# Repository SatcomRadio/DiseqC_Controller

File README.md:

# DiseqC_Controller
Controller board based on a ESP32 to control DiseqC rotors

### This repo is a work in progress! Eveything is subject to change!

#### Please make sure to visit the [satcom radio website](https://satcomradio.github.io/)

----

### ESP32 image

First install nanoframework:  
In a powershell window write: `dotnet tool install -g nanoff`  
Check [this link](https://github.com/nanoframework/nanoFirmwareFlasher) for more information

If you want to build the code:  

Install nanoframework on the ESP32 C3 with the command:
`nanoff --update --target XIAO_ESP32C3 --serialport COM{YOUR NUMBER} --masserase`  

Then compile the code and upload  

If you only want to flash the Diseq controller to your ESP32:  

`nanoff --target XIAO_ESP32C3 --update --serialport COM{YOUR NUMBER} --deploy --image "c:\PATH_TO_YOUR\DiseqC.bin"`  

----

### General info

Before connecting the rotor, ADJUST THE VOLTAGE to around 18v max!  
To do so, send the command to move the rotor, monitor the voltage in the SMA output and adjust the trimmer.

When turning the controller on the status led will flash fast to indicate that it's trying to connect to your wifi.

When there's no wifi configured or it didn't managed to connect, the ESP32 will create it's own access point and the led will flash slowly.  
Connect to it and use the rotor controller at:
`http://192.168.5.1`

If the controller manages to connect to your wifi, the status led will be on continuously.  
Check it's IP address on your modem page.

You can also send an angle using a POST to the following API:

The potentiometer works in intervals of 20º. It's not linear due to limitations of the ESP32
You can check the current value on the website and mark it down with a pen in the metal case.

----

### Construction:

Make sure to trim the solder fillets at the bottom of the step up converter. 
It's the only difficult part to sodler as you need that it makes a good contact with the tabs at the bottom

Fold the leds before soldering them as shown in previous pictures.

----

### Ordering the PCB:

Download the Gerber file from this repo and order it a jlcpcb with the default options.  
The only option I've changed is to remove the manufacture code mark

----

### BOM:

- [80x32x32 mm case](https://aliexpress.com/item/1005005484479479.html)
- [ESP32 C3 super mini with antenna port](https://aliexpress.com/item/1005007785335513.html)
- [SMA Edge connector](https://aliexpress.com/item/1005007013777316.html)
- [UFL pigtail](https://aliexpress.com/item/1005009270045616.html)
- 2.54mm Header pins (usually included with the ESP32)
- 0805 capacitor 10u
- 0805 capacitor 4.7n
- 0805 capacitor 47n
- 0805 capacitor 10u
- 0805 resistor 4k7
- 0805 resistor 100
- 0805 resistor 50
- 0805 resistor 10k
- 0805 resistor 150
- 0805 resistor 20
- [12x12 1m CDRH125 inductor](https://aliexpress.com/item/1005002743197146.html)
- [3mm 3v led](https://aliexpress.com/item/1005006269054479.html)
- [AO4484](https://aliexpress.com/item/1005009121264682.html)
- [TL081CDR](https://aliexpress.com/item/1005007336116897.html)
- [MT-3608 Step up module](https://aliexpress.com/item/1005007723986240.html)
- [10k potentiometer with button](https://aliexpress.com/item/1005009506482081.html)

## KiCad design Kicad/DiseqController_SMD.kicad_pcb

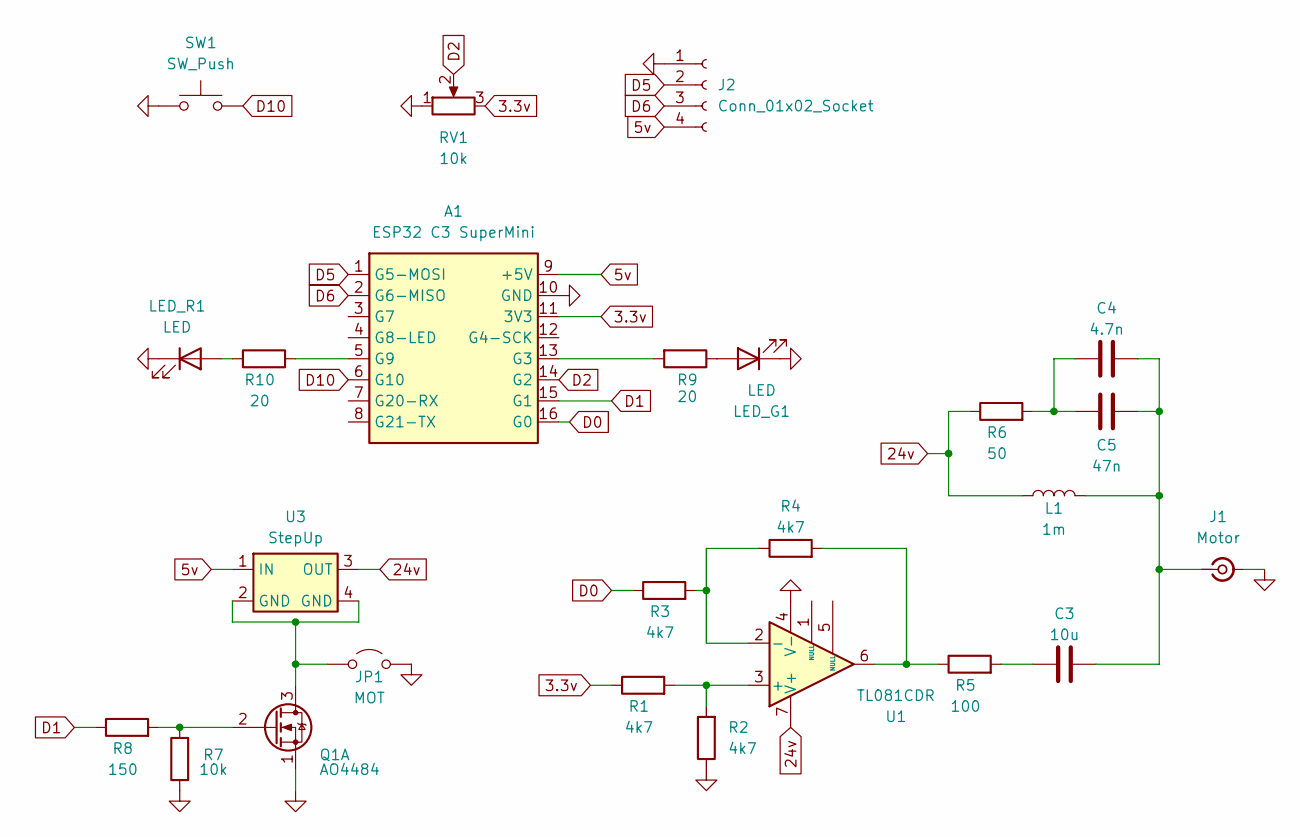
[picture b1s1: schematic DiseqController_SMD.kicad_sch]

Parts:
A1: ESP32 C3 SuperMini; ESP32SuperMini
C3: 10u; C_0805_2012Metric_Pad1.18x1.45mm_HandSolder
C4: 4.7n; C_0805_2012Metric_Pad1.18x1.45mm_HandSolder
C5: 47n; C_0805_2012Metric_Pad1.18x1.45mm_HandSolder
J1: Motor; SMA_Edge
J2: Conn_01x02_Socket; PinHeader_1x04_P2.54mm_Vertical
JP1: MOT; SolderJumper-2_P1.3mm_Open_Pad1.0x1.5mm
L1: 1m; Indcutor_12x12mm_H6mm
LED_G1: LED; Bent_LED_3mm
LED_R1: LED; Bent_LED_3mm
Q1: AO4484
R1, R2, R3, R4: 4k7; R_0805_2012Metric_Pad1.20x1.40mm_HandSolder
R5: 100; R_0805_2012Metric_Pad1.20x1.40mm_HandSolder
R6: 50; R_0805_2012Metric_Pad1.20x1.40mm_HandSolder
R7: 10k; R_0805_2012Metric_Pad1.20x1.40mm_HandSolder
R8: 150; R_0805_2012Metric_Pad1.20x1.40mm_HandSolder
R9, R10: 20; R_0805_2012Metric_Pad1.20x1.40mm_HandSolder
RV1: 10k; PinHeader_1x03_P2.54mm_Vertical
SW1: SW_Push; PinHeader_1x02_P2.54mm_Vertical
U1: TL081CDR; SOIC-8_3.9x4.9mm_P1.27mm
U3: StepUp; StepUp_2A

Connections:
3.3v: A1.11 (3V3), R1.1, RV1.3
5v: A1.9 (+5V), J2.4, U3.1 (IN)
24v: L1.1, R6.1, U1.7 (V+), U3.3 (OUT)
D0: A1.16 (G0), R3.1
D1: A1.15 (G1), R8.1
D2: A1.14 (G2), RV1.2
D5: A1.1 (G5-MOSI), J2.2
D6: A1.2 (G6-MISO), J2.3
D10: A1.6 (G10), SW1.2
GND: A1.10 (GND), J1.2 (Ext), J2.1, JP1.2 (B), LED_G1.1 (K), LED_R1.1 (K), Q1.1 (S1), R2.1, R7.1, RV1.1, SW1.1, U1.4 (V-)
unnamed: A1.13 (G3), R9.2
unnamed: A1.5 (G9), R10.2
unnamed: C3.2, R5.2
unnamed: C4.2, C5.2, R6.2
unnamed: C3.1, C4.1, C5.1, J1.1 (In), L1.2
unnamed: JP1.1 (A), Q1.3 (D1), U3.2 (GND), U3.4 (GND)
unnamed: LED_G1.2 (A), R9.1
unnamed: LED_R1.2 (A), R10.1
unnamed: Q1.2 (G1), R7.2, R8.2
unnamed: R4.2, R5.1, U1.6
unnamed: R1.2, R2.2, U1.3 (+)
unnamed: R3.2, R4.1, U1.2 (-)

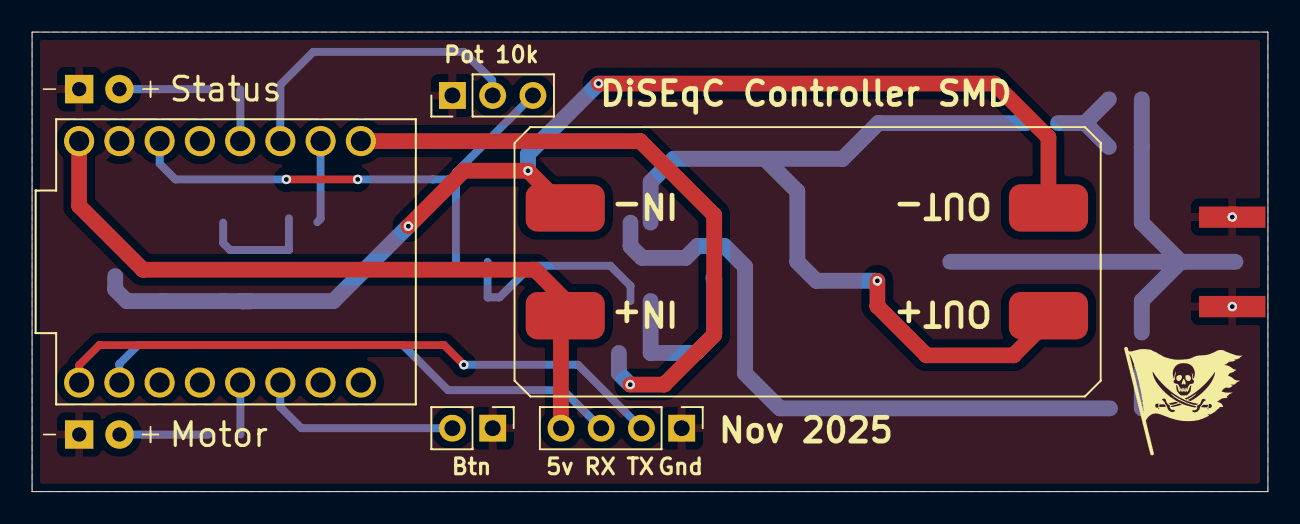
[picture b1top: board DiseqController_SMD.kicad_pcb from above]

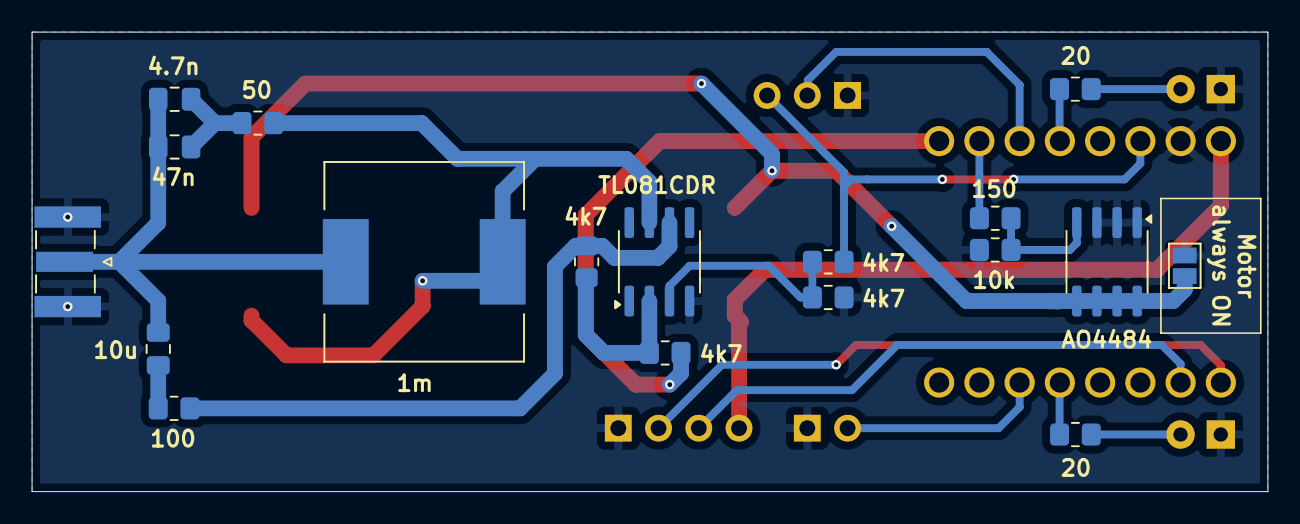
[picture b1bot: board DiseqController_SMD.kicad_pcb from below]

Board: 2 copper layers, 78.0 x 29.0 mm, 25 parts (18 on the bottom side), 22 nets.

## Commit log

2025-10-04 Added more info
2025-10-04 Fix silkscreen
2025-10-04 Added info
2025-10-04 Updated component
2025-10-06 Refactor
2025-10-06 uPDATE GITIGNORE
2025-10-22 code refactoring and fixes
2025-11-17 Added SMD version with more stuff
2025-11-22 Show pot position in web
2025-11-22 update info
2025-12-02 Added Gpredict support
